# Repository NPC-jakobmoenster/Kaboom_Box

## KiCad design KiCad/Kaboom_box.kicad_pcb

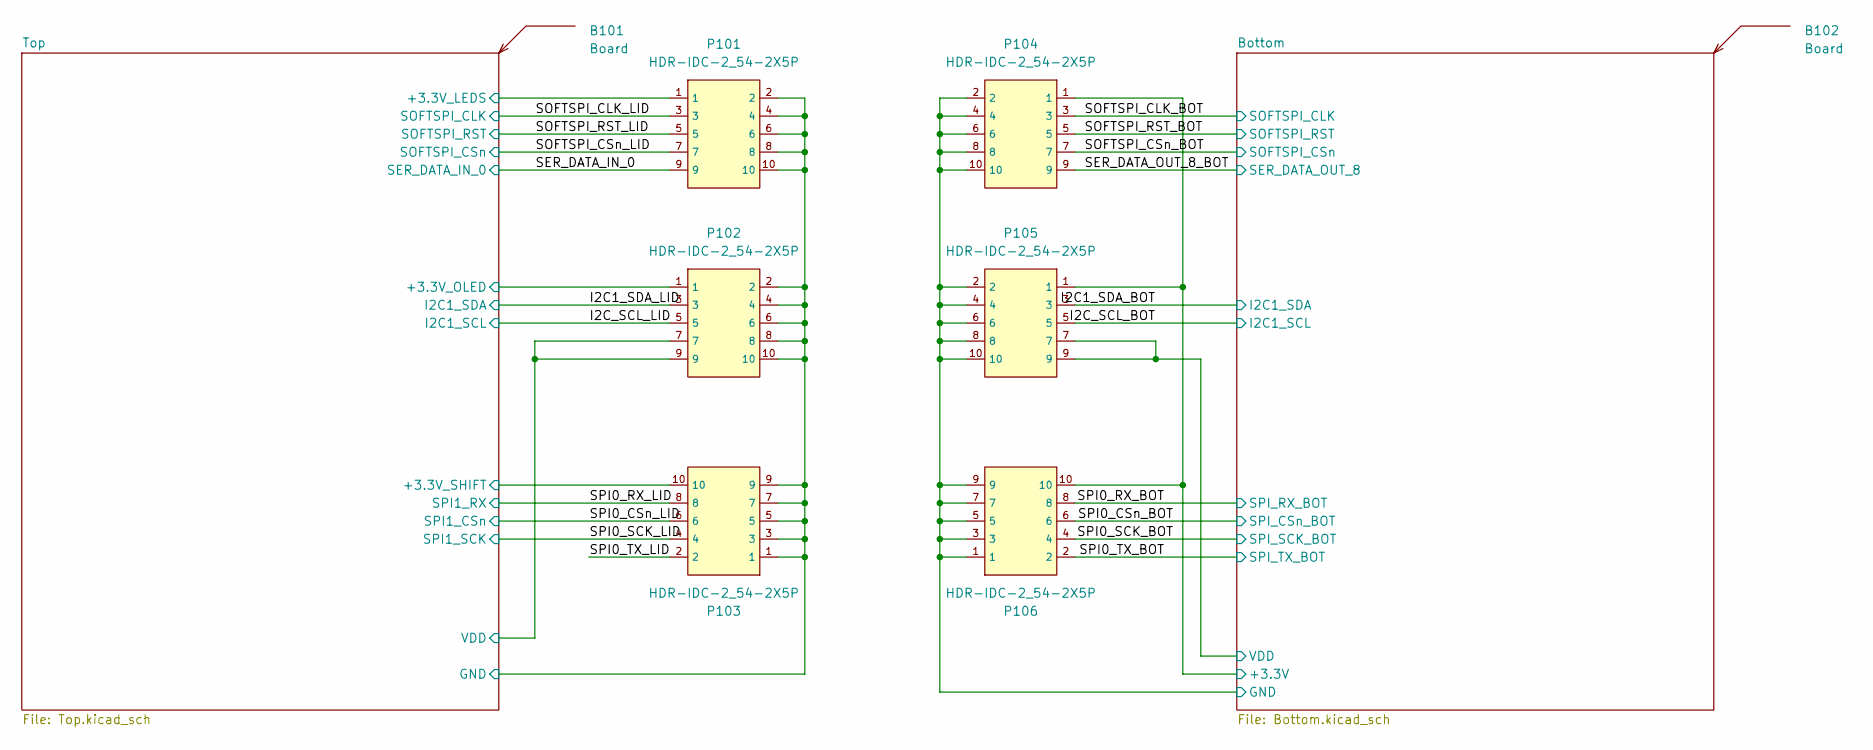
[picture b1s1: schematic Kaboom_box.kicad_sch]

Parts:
B101, B102: Board
P101, P102, P103, P104, P105, P106: HDR-IDC-2_54-2X5P; IDC-TH_10P-P2.54_C5665; LCSC C5665

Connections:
/Bottom/+3.3V: P104.1, P105.1, P106.10; also elsewhere on the board
/Bottom/VDD: P105.7, P105.9; also elsewhere on the board
/I2C1_SDA_BOT: P105.3; also elsewhere on the board
/I2C1_SDA_LID: P102.3; also elsewhere on the board
/I2C_SCL_BOT: P105.5; also elsewhere on the board
/I2C_SCL_LID: P102.5; also elsewhere on the board
/SER_DATA_IN_0: P101.9; also elsewhere on the board
/SER_DATA_OUT_8_BOT: P104.9; also elsewhere on the board
/SOFTSPI_CLK_BOT: P104.3; also elsewhere on the board
/SOFTSPI_CLK_LID: P101.3; also elsewhere on the board
/SOFTSPI_CSn_BOT: P104.7; also elsewhere on the board
/SOFTSPI_CSn_LID: P101.7; also elsewhere on the board
/SOFTSPI_RST_BOT: P104.5; also elsewhere on the board
/SOFTSPI_RST_LID: P101.5; also elsewhere on the board
/SPI0_CSn_BOT: P106.6; also elsewhere on the board
/SPI0_CSn_LID: P103.6; also elsewhere on the board
/SPI0_RX_BOT: P106.8; also elsewhere on the board
/SPI0_RX_LID: P103.8; also elsewhere on the board
/SPI0_SCK_BOT: P106.4; also elsewhere on the board
/SPI0_SCK_LID: P103.4; also elsewhere on the board
/SPI0_TX_BOT: P106.2; also elsewhere on the board
/SPI0_TX_LID: P103.2
/Top/+3.3V_LEDS: P101.1; also elsewhere on the board
/Top/+3.3V_OLED: P102.1; also elsewhere on the board
/Top/+3.3V_SHIFT: P103.10; also elsewhere on the board
/Top/GND: P101.2, P101.4, P101.6, P101.8, P101.10, P102.2, P102.4, P102.6, P102.8, P102.10, P103.1, P103.3, P103.5, P103.7, P103.9; also elsewhere on the board
/Top/VDD: P102.7, P102.9; also elsewhere on the board
GND: P104.2, P104.4, P104.6, P104.8, P104.10, P105.2, P105.4, P105.6, P105.8, P105.10, P106.1, P106.3, P106.5, P106.7, P106.9; also elsewhere on the board

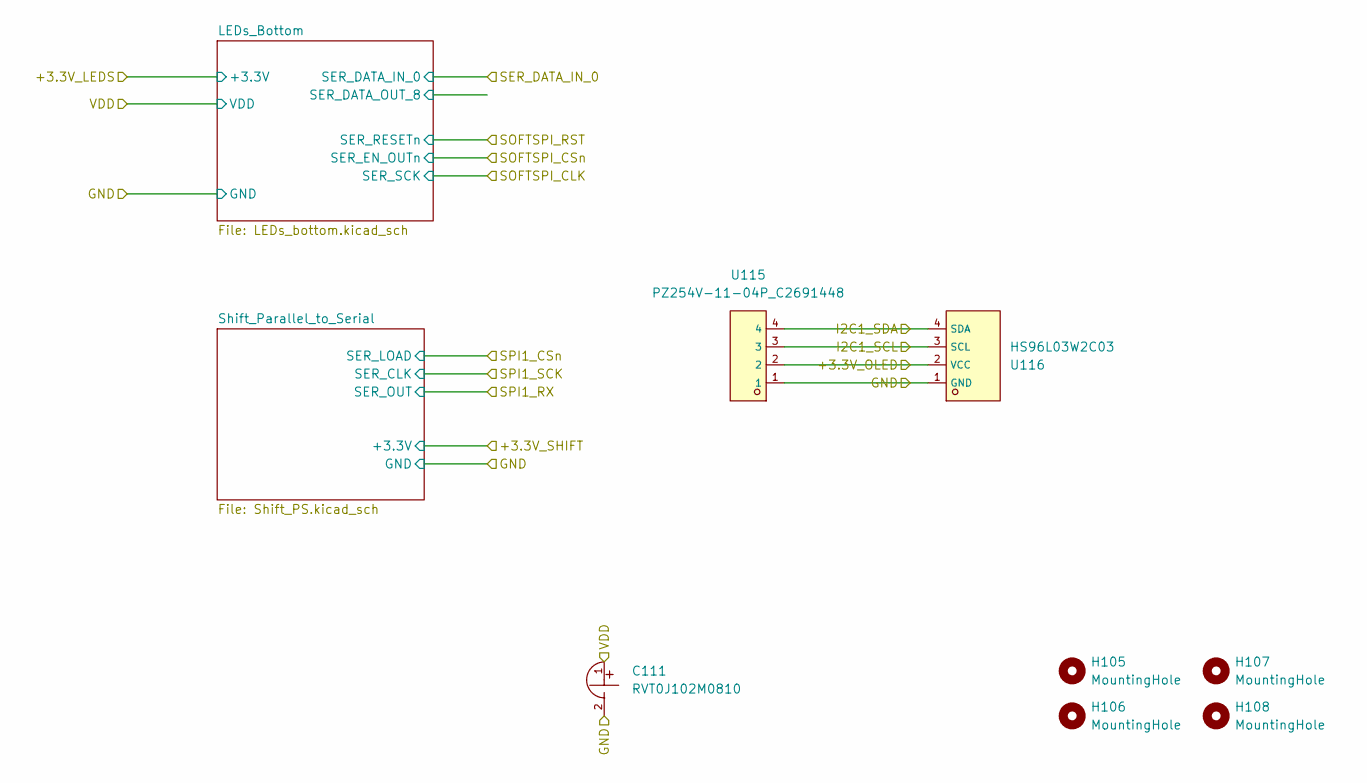
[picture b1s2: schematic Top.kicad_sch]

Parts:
C111: RVT0J102M0810; CAP-SMD_BD8.0-L8.3-W8.3-FD; LCSC C42851
H105, H106, H107, H108: MountingHole; MountingHole_4.3mm_M4
U115: PZ254V-11-04P_C2691448; HDR-TH_4P-P2.54-V-M; LCSC C2691448
U116: HS96L03W2C03; OLED-TH_L27.8-W27.2-P2.54_C9900033791; LCSC C5248080

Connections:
/I2C1_SDA_LID: U115.4, U116.4 (SDA); also elsewhere on the board
/I2C_SCL_LID: U115.3, U116.3 (SCL); also elsewhere on the board
/Top/+3.3V_OLED: U115.2, U116.2 (VCC); also elsewhere on the board
/Top/GND: C111.2, U115.1, U116.1 (GND); also elsewhere on the board
/Top/VDD: C111.1; also elsewhere on the board

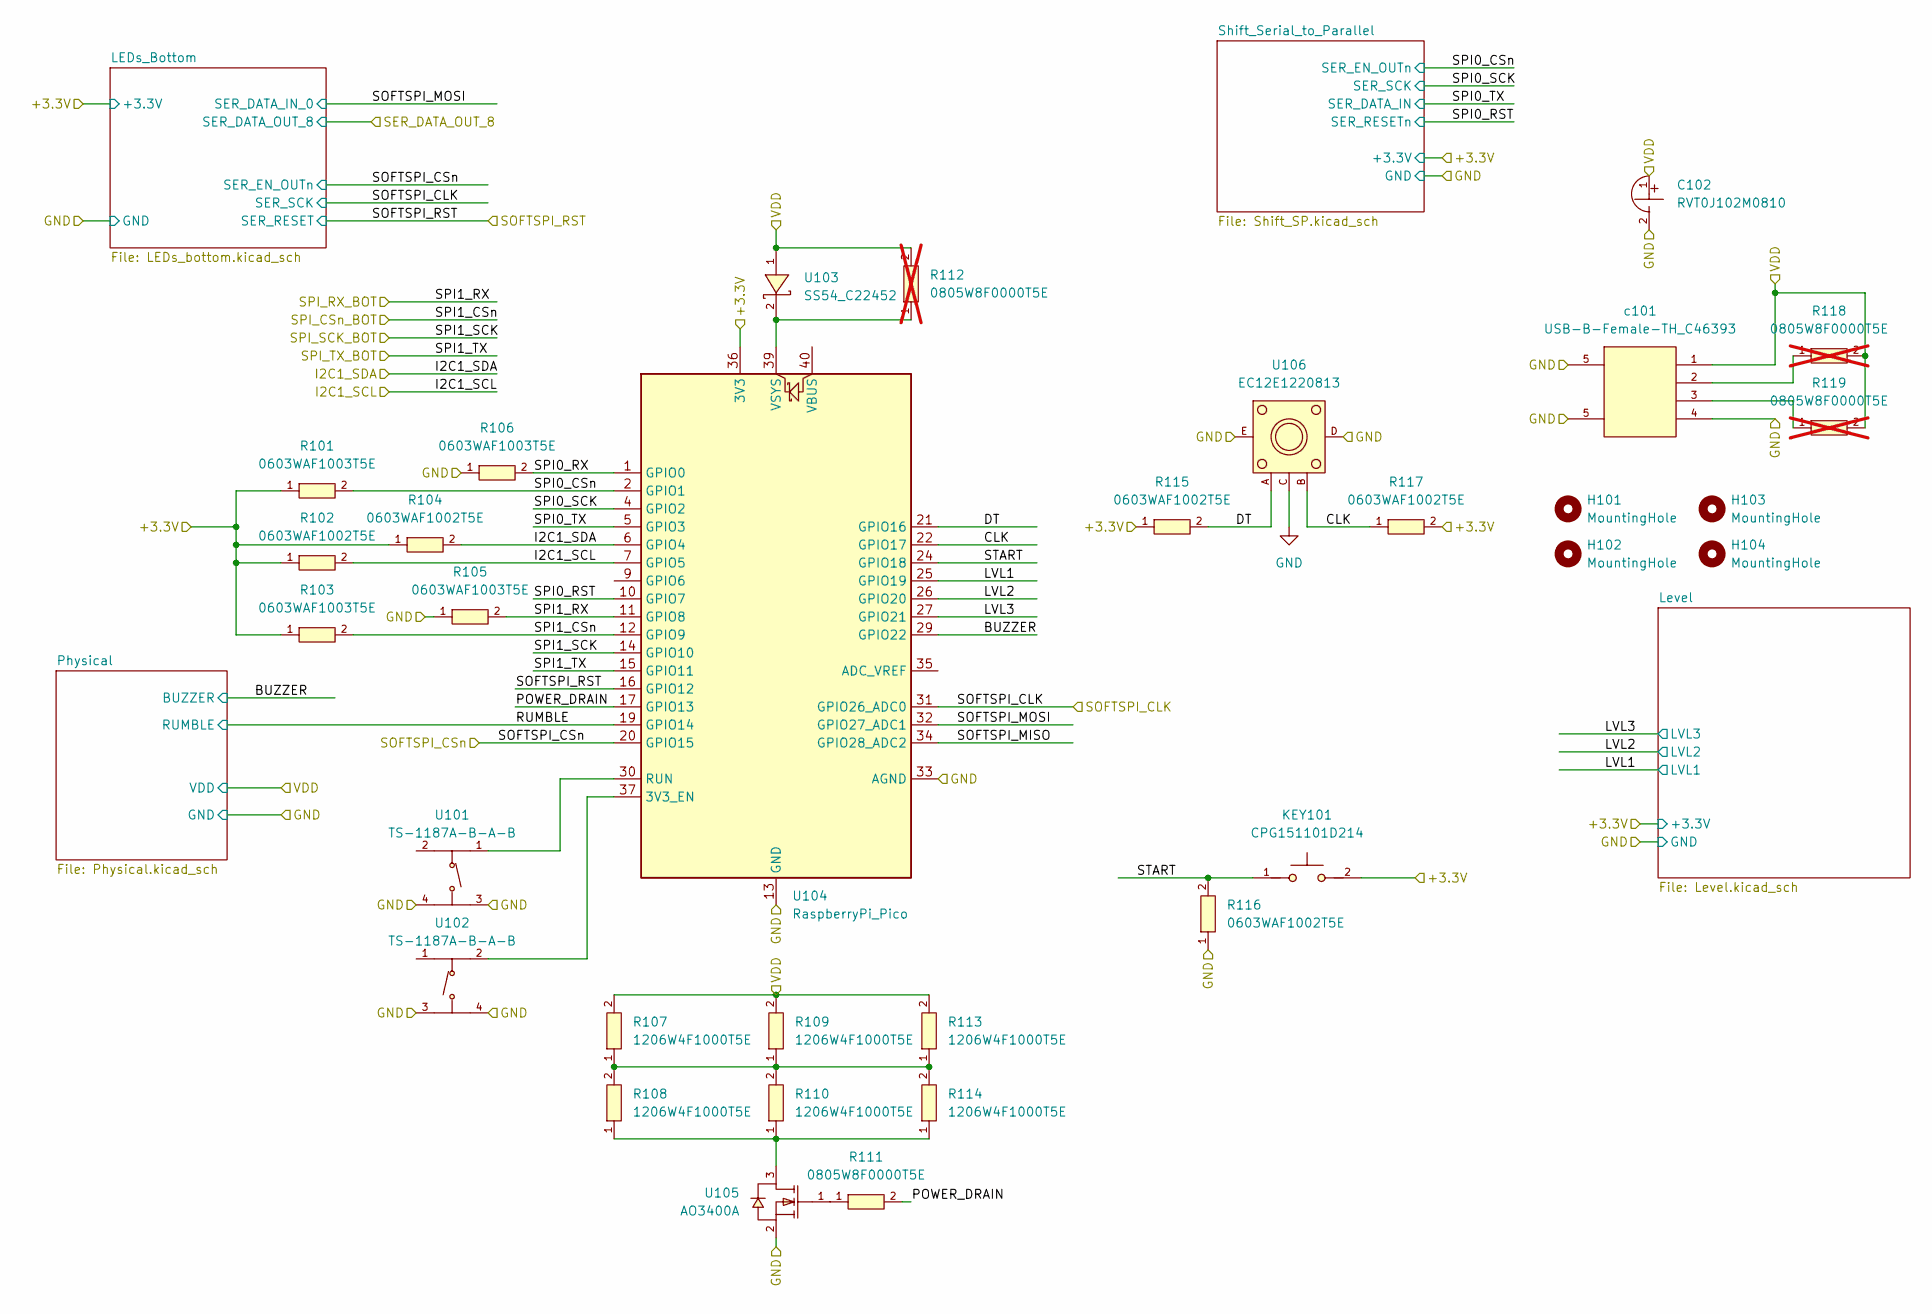
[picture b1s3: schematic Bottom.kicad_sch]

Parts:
C102: RVT0J102M0810; CAP-SMD_BD8.0-L8.3-W8.3-FD; LCSC C42851
H101, H102, H103, H104: MountingHole; MountingHole_4.3mm_M4
KEY101: CPG151101D214; KEY-TH_CPG151101D21X; LCSC C400232
R101, R103, R105, R106: 0603WAF1003T5E; R0603; LCSC C25803
R102, R104, R115, R116, R117: 0603WAF1002T5E; R0603; LCSC C25804
R107, R108, R109, R110, R113, R114: 1206W4F1000T5E; R1206; LCSC C17901
R111: 0805W8F0000T5E; R0805; LCSC C17477
R112, R118, R119: 0805W8F0000T5E; R0805; LCSC C17477; not fitted
U101, U102: TS-1187A-B-A-B; SW-SMD_4P-L5.1-W5.1-P3.70-LS6.5-TL-2; LCSC C318884
U103: SS54_C22452; SMA_L4.4-W2.8-LS5.4-R-RD; LCSC C22452
U104: RaspberryPi_Pico; RaspberryPi_Pico_Common_No_Keepout
U105: AO3400A; SOT-23-3_L2.9-W1.6-P1.90-LS2.8-BR; LCSC C20917
U106: EC12E1220813; SW-TH_EC12E1220813; LCSC C129727
c101: USB-B-Female-TH_C46393; USB-B_TH_BF90; LCSC C46393

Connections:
/Bottom/+3.3V: KEY101.2, R101.1, R102.1, R103.1, R104.1, R115.1, R117.2, U104.36 (3V3); also elsewhere on the board
/Bottom/BUZZER: U104.29 (GPIO22); also elsewhere on the board
/Bottom/CLK: R117.1, U104.22 (GPIO17), U106.B
/Bottom/DT: R115.2, U104.21 (GPIO16), U106.A
/Bottom/LVL1: U104.25 (GPIO19); also elsewhere on the board
/Bottom/LVL2: U104.26 (GPIO20); also elsewhere on the board
/Bottom/LVL3: U104.27 (GPIO21); also elsewhere on the board
/Bottom/POWER_DRAIN: R111.2, U104.17 (GPIO13)
/Bottom/RUMBLE: U104.19 (GPIO14); also elsewhere on the board
/Bottom/SOFTSPI_MISO: U104.34 (GPIO28_ADC2)
/Bottom/SOFTSPI_MOSI: U104.32 (GPIO27_ADC1); also elsewhere on the board
/Bottom/SPI0_CSn: R101.2, U104.2 (GPIO1); also elsewhere on the board
/Bottom/SPI0_RST: U104.10 (GPIO7); also elsewhere on the board
/Bottom/SPI0_RX: R106.2, U104.1 (GPIO0)
/Bottom/SPI0_SCK: U104.4 (GPIO2); also elsewhere on the board
/Bottom/SPI0_TX: U104.5 (GPIO3); also elsewhere on the board
/Bottom/START: KEY101.1, R116.2, U104.24 (GPIO18)
/Bottom/VDD: C102.1, R107.2, R109.2, R112.2, R113.2, R118.2, R119.2, U103.1 (A), c101.1 (VCC); also elsewhere on the board
/I2C1_SDA_BOT: R104.2, U104.6 (GPIO4); also elsewhere on the board
/I2C_SCL_BOT: R102.2, U104.7 (GPIO5); also elsewhere on the board
/SOFTSPI_CLK_BOT: U104.31 (GPIO26_ADC0); also elsewhere on the board
/SOFTSPI_CSn_BOT: U104.20 (GPIO15); also elsewhere on the board
/SOFTSPI_RST_BOT: U104.16 (GPIO12); also elsewhere on the board
/SPI0_CSn_BOT: R103.2, U104.12 (GPIO9); also elsewhere on the board
/SPI0_RX_BOT: R105.2, U104.11 (GPIO8); also elsewhere on the board
/SPI0_SCK_BOT: U104.14 (GPIO10); also elsewhere on the board
/SPI0_TX_BOT: U104.15 (GPIO11); also elsewhere on the board
GND: C102.2, R105.1, R106.1, R116.1, U101.3 (C), U101.4 (D), U102.3 (C), U102.4 (D), U104.3 (GND), U104.8 (GND), U104.13 (GND), U104.18 (GND), U104.23 (GND), U104.28 (GND), U104.33 (AGND), U104.38 (GND), U105.2 (S), U106.C, U106.D, U106.E, c101.4 (GND), c101.5 (EH); also elsewhere on the board
unnamed: R107.1, R108.2, R109.1, R110.2, R113.1, R114.2
unnamed: U101.1 (A), U104.30 (RUN)
unnamed: U102.2 (B), U104.37 (3V3_EN)
unnamed: R112.1, U103.2 (K), U104.39 (VSYS)
unnamed: R108.1, R110.1, R114.1, U105.3 (D)
unnamed: R111.1, U105.1 (G)
unnamed: R119.1, c101.3 (D+)
unnamed: R118.1, c101.2 (D-)

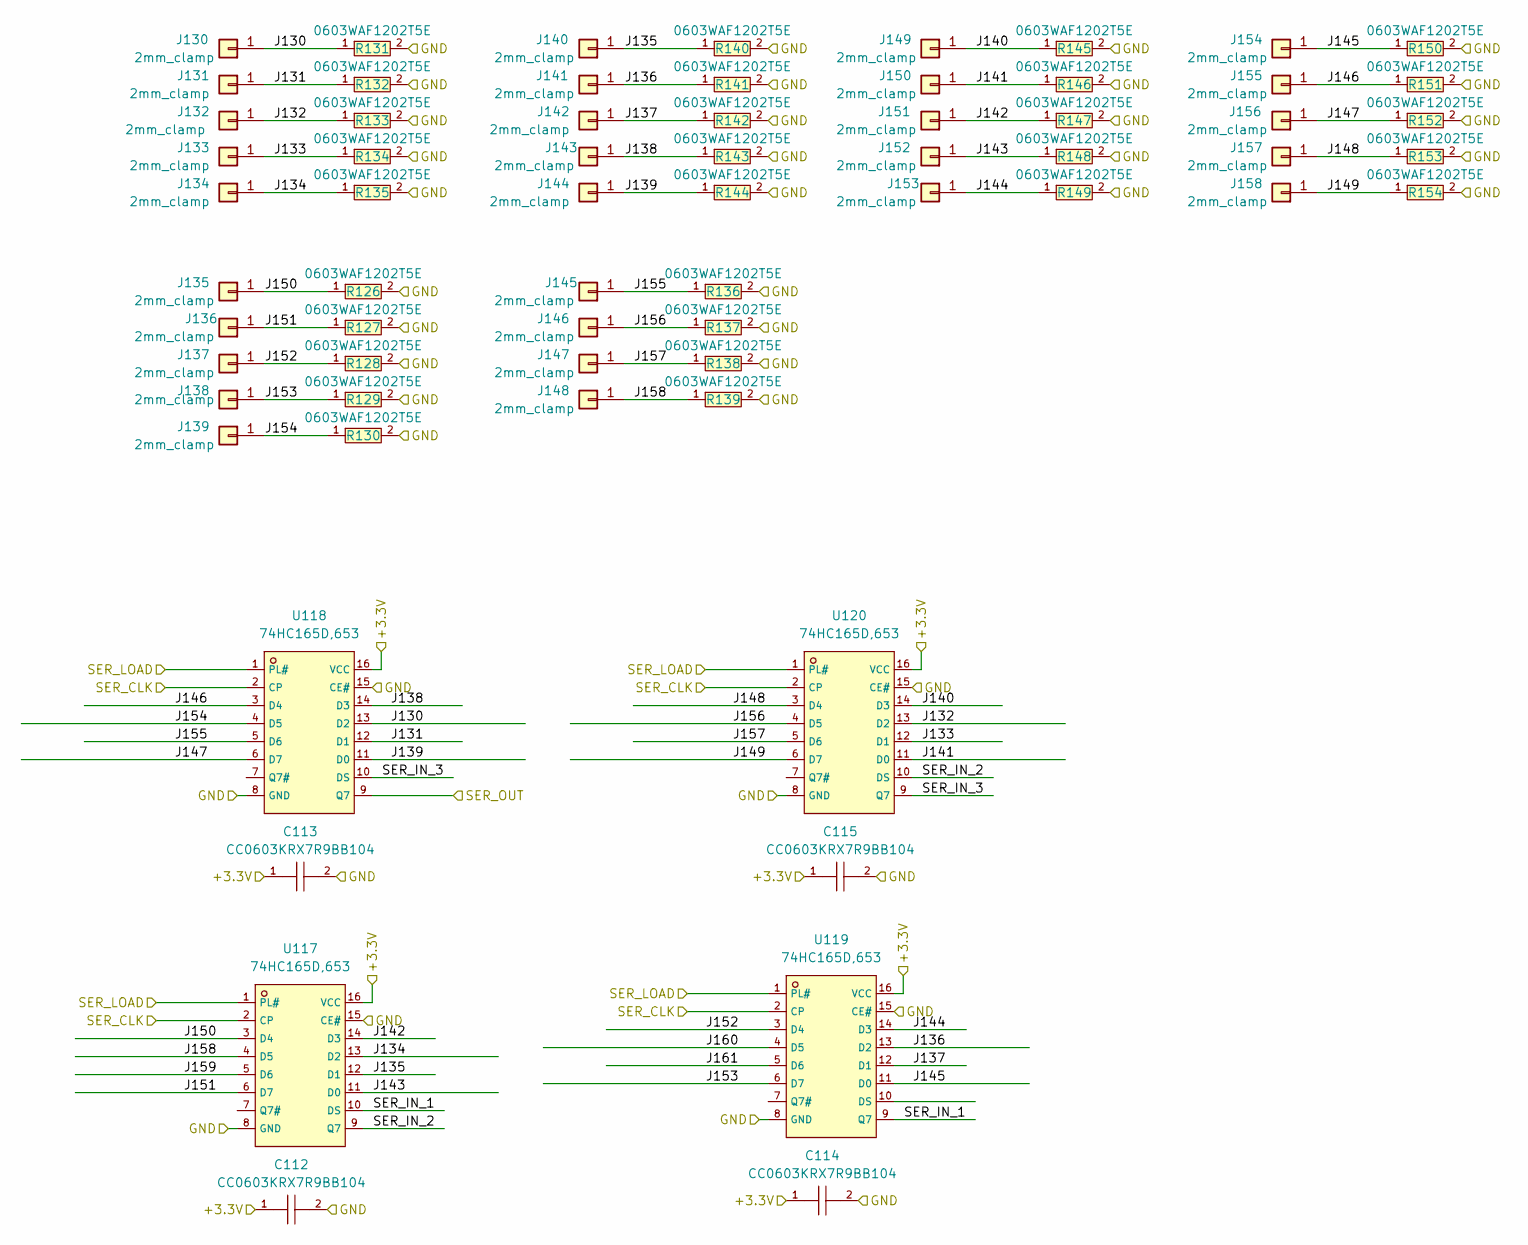
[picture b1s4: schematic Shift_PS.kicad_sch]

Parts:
C112, C113, C114, C115: CC0603KRX7R9BB104; C0603; LCSC C14663
J130, J131, J132, J133, J134, J135, J136, J137, J138, J139, J140, J141, J142, J143, J144, J145, J146, J147, J148, J149, J150, J151, J152, J153, J154, J155, J156, J157, J158: 2mm_clamp; 2mm testlead, screw-clamp
R126, R127, R128, R129, R130, R131, R132, R133, R134, R135, R136, R137, R138, R139, R140, R141, R142, R143, R144, R145, R146, R147, R148, R149, R150, R151, R152, R153, R154: 0603WAF1202T5E; R0603; LCSC C22790
U117, U118, U119, U120: 74HC165D,653; SOIC-16_L9.9-W3.9-P1.27-LS6.0-BL; LCSC C5613

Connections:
/SPI0_CSn_LID: U117.1 (PL#), U118.1 (PL#), U119.1 (PL#), U120.1 (PL#); also elsewhere on the board
/SPI0_RX_LID: U118.9 (Q7); also elsewhere on the board
/SPI0_SCK_LID: U117.2 (CP), U118.2 (CP), U119.2 (CP), U120.2 (CP); also elsewhere on the board
/Top/+3.3V_SHIFT: C112.1, C113.1, C114.1, C115.1, U117.16 (VCC), U118.16 (VCC), U119.16 (VCC), U120.16 (VCC); also elsewhere on the board
/Top/GND: C112.2, C113.2, C114.2, C115.2, R126.2, R127.2, R128.2, R129.2, R130.2, R131.2, R132.2, R133.2, R134.2, R135.2, R136.2, R137.2, R138.2, R139.2, R140.2, R141.2, R142.2, R143.2, R144.2, R145.2, R146.2, R147.2, R148.2, R149.2, R150.2, R151.2, R152.2, R153.2, R154.2, U117.8 (GND), U117.15 (CE#), U118.8 (GND), U118.15 (CE#), U119.8 (GND), U119.15 (CE#), U120.8 (GND), U120.15 (CE#); also elsewhere on the board
/Top/Shift_Parallel_to_Serial/J130: J130.1, R131.1, U118.13 (D2)
/Top/Shift_Parallel_to_Serial/J131: J131.1, R132.1, U118.12 (D1)
/Top/Shift_Parallel_to_Serial/J132: J132.1, R133.1, U120.13 (D2)
/Top/Shift_Parallel_to_Serial/J133: J133.1, R134.1, U120.12 (D1)
/Top/Shift_Parallel_to_Serial/J134: J134.1, R135.1, U117.13 (D2)
/Top/Shift_Parallel_to_Serial/J135: J140.1, R140.1, U117.12 (D1)
/Top/Shift_Parallel_to_Serial/J136: J141.1, R141.1, U119.13 (D2)
/Top/Shift_Parallel_to_Serial/J137: J142.1, R142.1, U119.12 (D1)
/Top/Shift_Parallel_to_Serial/J138: J143.1, R143.1, U118.14 (D3)
/Top/Shift_Parallel_to_Serial/J139: J144.1, R144.1, U118.11 (D0)
/Top/Shift_Parallel_to_Serial/J140: J149.1, R145.1, U120.14 (D3)
/Top/Shift_Parallel_to_Serial/J141: J150.1, R146.1, U120.11 (D0)
/Top/Shift_Parallel_to_Serial/J142: J151.1, R147.1, U117.14 (D3)
/Top/Shift_Parallel_to_Serial/J143: J152.1, R148.1, U117.11 (D0)
/Top/Shift_Parallel_to_Serial/J144: J153.1, R149.1, U119.14 (D3)
/Top/Shift_Parallel_to_Serial/J145: J154.1, R150.1, U119.11 (D0)
/Top/Shift_Parallel_to_Serial/J146: J155.1, R151.1, U118.3 (D4)
/Top/Shift_Parallel_to_Serial/J147: J156.1, R152.1, U118.6 (D7)
/Top/Shift_Parallel_to_Serial/J148: J157.1, R153.1, U120.3 (D4)
/Top/Shift_Parallel_to_Serial/J149: J158.1, R154.1, U120.6 (D7)
/Top/Shift_Parallel_to_Serial/J150: J135.1, R126.1, U117.3 (D4)
/Top/Shift_Parallel_to_Serial/J151: J136.1, R127.1, U117.6 (D7)
/Top/Shift_Parallel_to_Serial/J152: J137.1, R128.1, U119.3 (D4)
/Top/Shift_Parallel_to_Serial/J153: J138.1, R129.1, U119.6 (D7)
/Top/Shift_Parallel_to_Serial/J154: J139.1, R130.1, U118.4 (D5)
/Top/Shift_Parallel_to_Serial/J155: J145.1, R136.1, U118.5 (D6)
/Top/Shift_Parallel_to_Serial/J156: J146.1, R137.1, U120.4 (D5)
/Top/Shift_Parallel_to_Serial/J157: J147.1, R138.1, U120.5 (D6)
/Top/Shift_Parallel_to_Serial/J158: J148.1, R139.1, U117.4 (D5)
/Top/Shift_Parallel_to_Serial/J159: U117.5 (D6)
/Top/Shift_Parallel_to_Serial/J160: U119.4 (D5)
/Top/Shift_Parallel_to_Serial/J161: U119.5 (D6)
/Top/Shift_Parallel_to_Serial/SER_IN_1: U117.10 (DS), U119.9 (Q7)
/Top/Shift_Parallel_to_Serial/SER_IN_2: U117.9 (Q7), U120.10 (DS)
/Top/Shift_Parallel_to_Serial/SER_IN_3: U118.10 (DS), U120.9 (Q7)

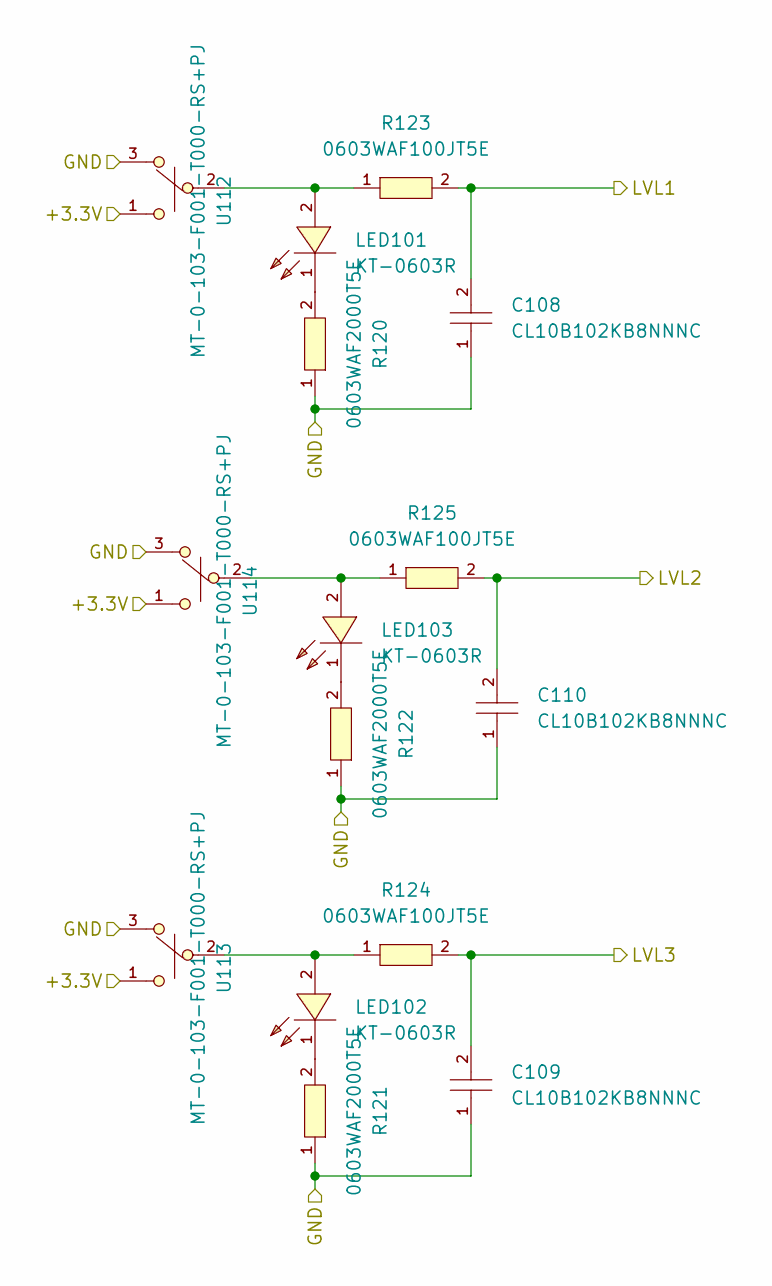
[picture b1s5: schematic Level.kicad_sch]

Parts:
C108, C109, C110: CL10B102KB8NNNC; C0603; LCSC C1588
LED101, LED102, LED103: KT-0603R; LED0603-RD; LCSC C2286
R120, R121, R122: 0603WAF2000T5E; R0603; LCSC C8218
R123, R124, R125: 0603WAF100JT5E; R0603; LCSC C22859
U112, U113, U114: MT-0-103-F001-T000-RS+PJ; SW-TH_MT-0-103-A101-M200-RS; LCSC C1788498

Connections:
/Bottom/+3.3V: U112.1, U113.1, U114.1; also elsewhere on the board
/Bottom/LVL1: C108.2, R123.2; also elsewhere on the board
/Bottom/LVL2: C110.2, R125.2; also elsewhere on the board
/Bottom/LVL3: C109.2, R124.2; also elsewhere on the board
GND: C108.1, C109.1, C110.1, R120.1, R121.1, R122.1, U112.3, U113.3, U114.3; also elsewhere on the board
unnamed: LED101.2 (A), R123.1, U112.2
unnamed: LED101.1 (K), R120.2
unnamed: LED102.2 (A), R124.1, U113.2
unnamed: LED102.1 (K), R121.2
unnamed: LED103.2 (A), R125.1, U114.2
unnamed: LED103.1 (K), R122.2

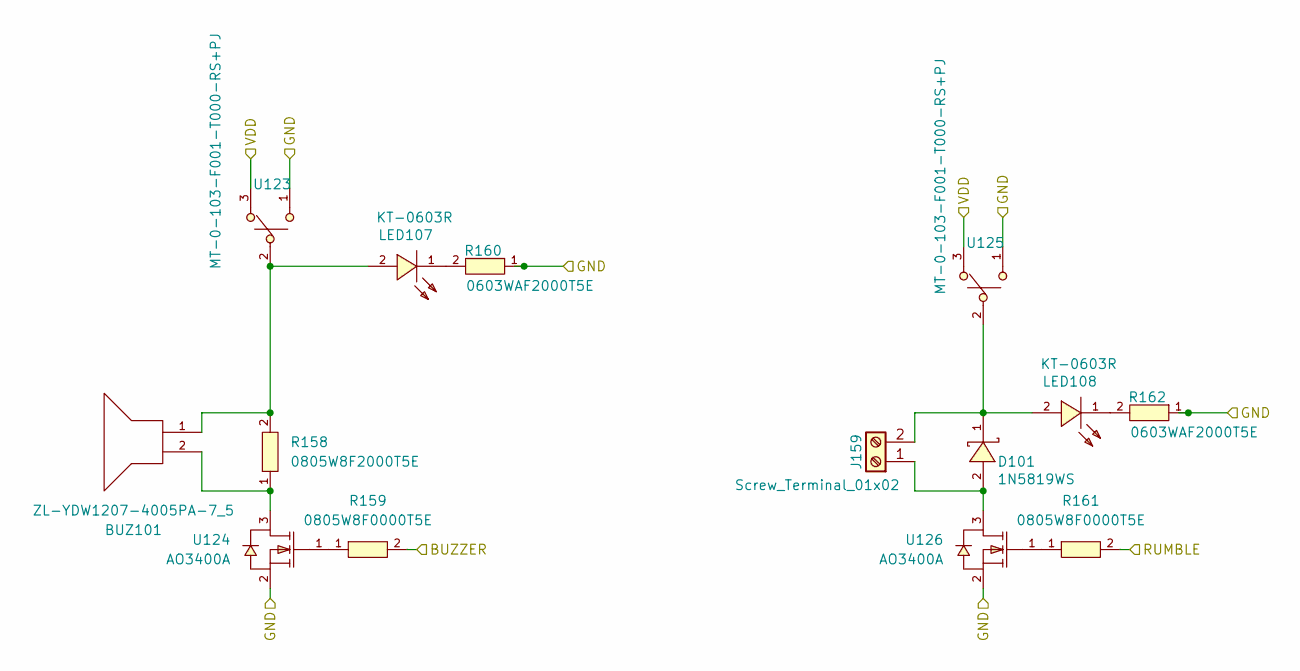
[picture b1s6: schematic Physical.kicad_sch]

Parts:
BUZ101: ZL-YDW1207-4005PA-7_5; BUZ-TH_BD12.6-P7.50-D0.9; LCSC C219725
D101: 1N5819WS; SOD-323_L1.8-W1.3-LS2.5-RD; LCSC C191023
J159: Screw_Terminal_01x02; TerminalBlock_Phoenix_MKDS-1,5-2_1x02_P5.00mm_Horizontal
LED107, LED108: KT-0603R; LED0603-RD; LCSC C2286
R158: 0805W8F2000T5E; R0805; LCSC C17540
R159, R161: 0805W8F0000T5E; R0805; LCSC C17477
R160, R162: 0603WAF2000T5E; R0603; LCSC C8218
U123, U125: MT-0-103-F001-T000-RS+PJ; SW-TH_MT-0-103-A101-M200-RS; LCSC C1788498
U124, U126: AO3400A; SOT-23-3_L2.9-W1.6-P1.90-LS2.8-BR; LCSC C20917

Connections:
/Bottom/BUZZER: R159.2; also elsewhere on the board
/Bottom/RUMBLE: R161.2; also elsewhere on the board
/Bottom/VDD: U123.3, U125.3; also elsewhere on the board
GND: R160.1, R162.1, U123.1, U124.2 (S), U125.1, U126.2 (S); also elsewhere on the board
unnamed: D101.2 (A), J159.1, U126.3 (D)
unnamed: D101.1 (K), J159.2, LED108.2 (A), U125.2
unnamed: BUZ101.1, LED107.2 (A), R158.2, U123.2
unnamed: LED107.1 (K), R160.2
unnamed: LED108.1 (K), R162.2
unnamed: BUZ101.2, R158.1, U124.3 (D)
unnamed: R159.1, U124.1 (G)
unnamed: R161.1, U126.1 (G)

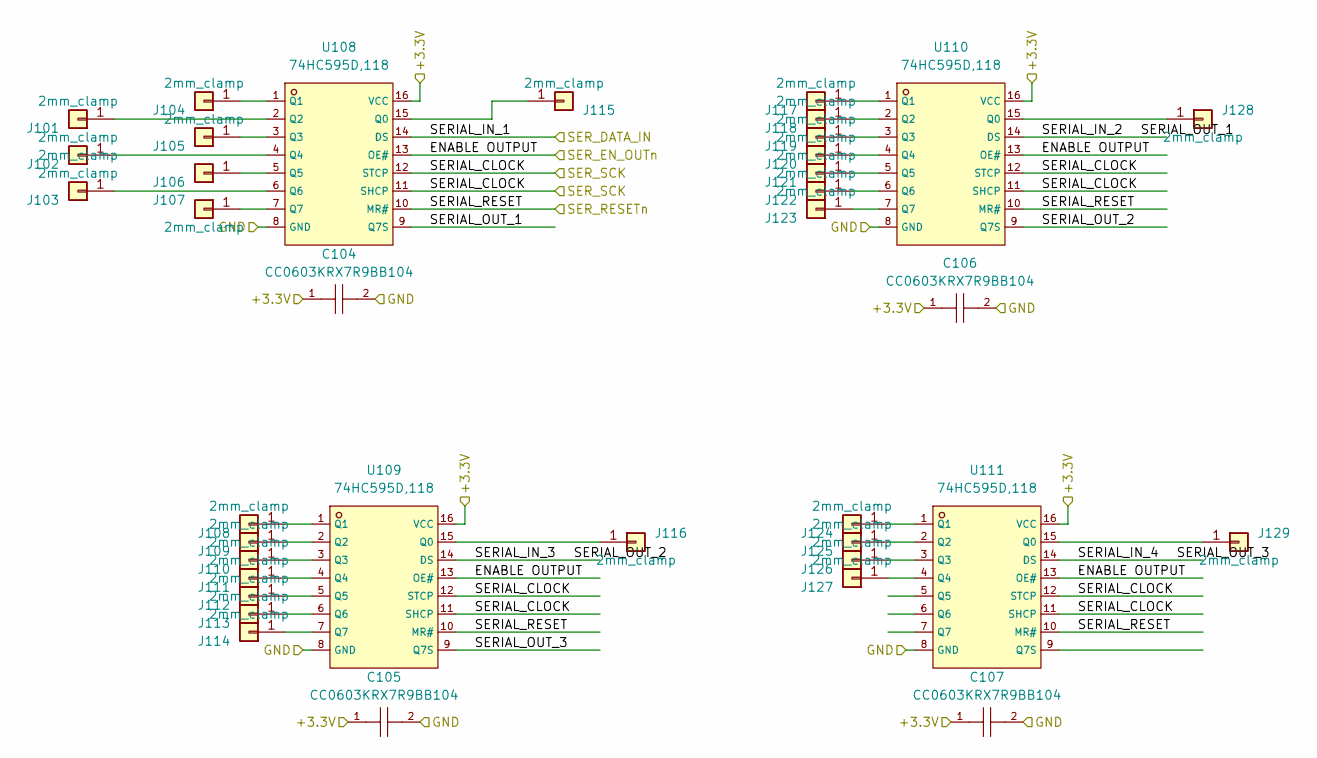
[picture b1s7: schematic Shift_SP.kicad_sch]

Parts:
C104, C105, C106, C107: CC0603KRX7R9BB104; C0603; LCSC C14663
J101, J102, J103, J104, J105, J106, J107, J108, J109, J110, J111, J112, J113, J114, J115, J116, J117, J118, J119, J120, J121, J122, J123, J124, J125, J126, J127, J128, J129: 2mm_clamp; 2mm testlead, screw-clamp
U108, U109, U110, U111: 74HC595D,118; SOIC-16_L9.9-W3.9-P1.27-LS6.0-BL; LCSC C5947

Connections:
/Bottom/+3.3V: C104.1, C105.1, C106.1, C107.1, U108.16 (VCC), U109.16 (VCC), U110.16 (VCC), U111.16 (VCC); also elsewhere on the board
/Bottom/SPI0_CSn: U108.13 (OE#), U109.13 (OE#), U110.13 (OE#), U111.13 (OE#); also elsewhere on the board
/Bottom/SPI0_RST: U108.10 (MR#), U109.10 (MR#), U110.10 (MR#), U111.10 (MR#); also elsewhere on the board
/Bottom/SPI0_SCK: U108.11 (SHCP), U108.12 (STCP), U109.11 (SHCP), U109.12 (STCP), U110.11 (SHCP), U110.12 (STCP), U111.11 (SHCP), U111.12 (STCP); also elsewhere on the board
/Bottom/SPI0_TX: U108.14 (DS); also elsewhere on the board
/Bottom/Shift_Serial_to_Parallel/SERIAL_IN_2: U108.9 (Q7S), U110.14 (DS)
/Bottom/Shift_Serial_to_Parallel/SERIAL_IN_3: U109.14 (DS), U110.9 (Q7S)
/Bottom/Shift_Serial_to_Parallel/SERIAL_IN_4: U109.9 (Q7S), U111.14 (DS)
GND: C104.2, C105.2, C106.2, C107.2, U108.8 (GND), U109.8 (GND), U110.8 (GND), U111.8 (GND); also elsewhere on the board
unnamed: J101.1, U108.2 (Q2)
unnamed: J102.1, U108.4 (Q4)
unnamed: J103.1, U108.6 (Q6)
unnamed: J104.1, U108.1 (Q1)
unnamed: J105.1, U108.3 (Q3)
unnamed: J106.1, U108.5 (Q5)
unnamed: J107.1, U108.7 (Q7)
unnamed: J108.1, U109.1 (Q1)
unnamed: J109.1, U109.2 (Q2)
unnamed: J110.1, U109.3 (Q3)
unnamed: J111.1, U109.4 (Q4)
unnamed: J112.1, U109.5 (Q5)
unnamed: J113.1, U109.6 (Q6)
unnamed: J114.1, U109.7 (Q7)
unnamed: J115.1, U108.15 (Q0)
unnamed: J116.1, U109.15 (Q0)
unnamed: J117.1, U110.1 (Q1)
unnamed: J118.1, U110.2 (Q2)
unnamed: J119.1, U110.3 (Q3)
unnamed: J120.1, U110.4 (Q4)
unnamed: J121.1, U110.5 (Q5)
unnamed: J122.1, U110.6 (Q6)
unnamed: J123.1, U110.7 (Q7)
unnamed: J124.1, U111.1 (Q1)
unnamed: J125.1, U111.2 (Q2)
unnamed: J126.1, U111.3 (Q3)
unnamed: J127.1, U111.4 (Q4)
unnamed: J128.1, U110.15 (Q0)
unnamed: J129.1, U111.15 (Q0)
